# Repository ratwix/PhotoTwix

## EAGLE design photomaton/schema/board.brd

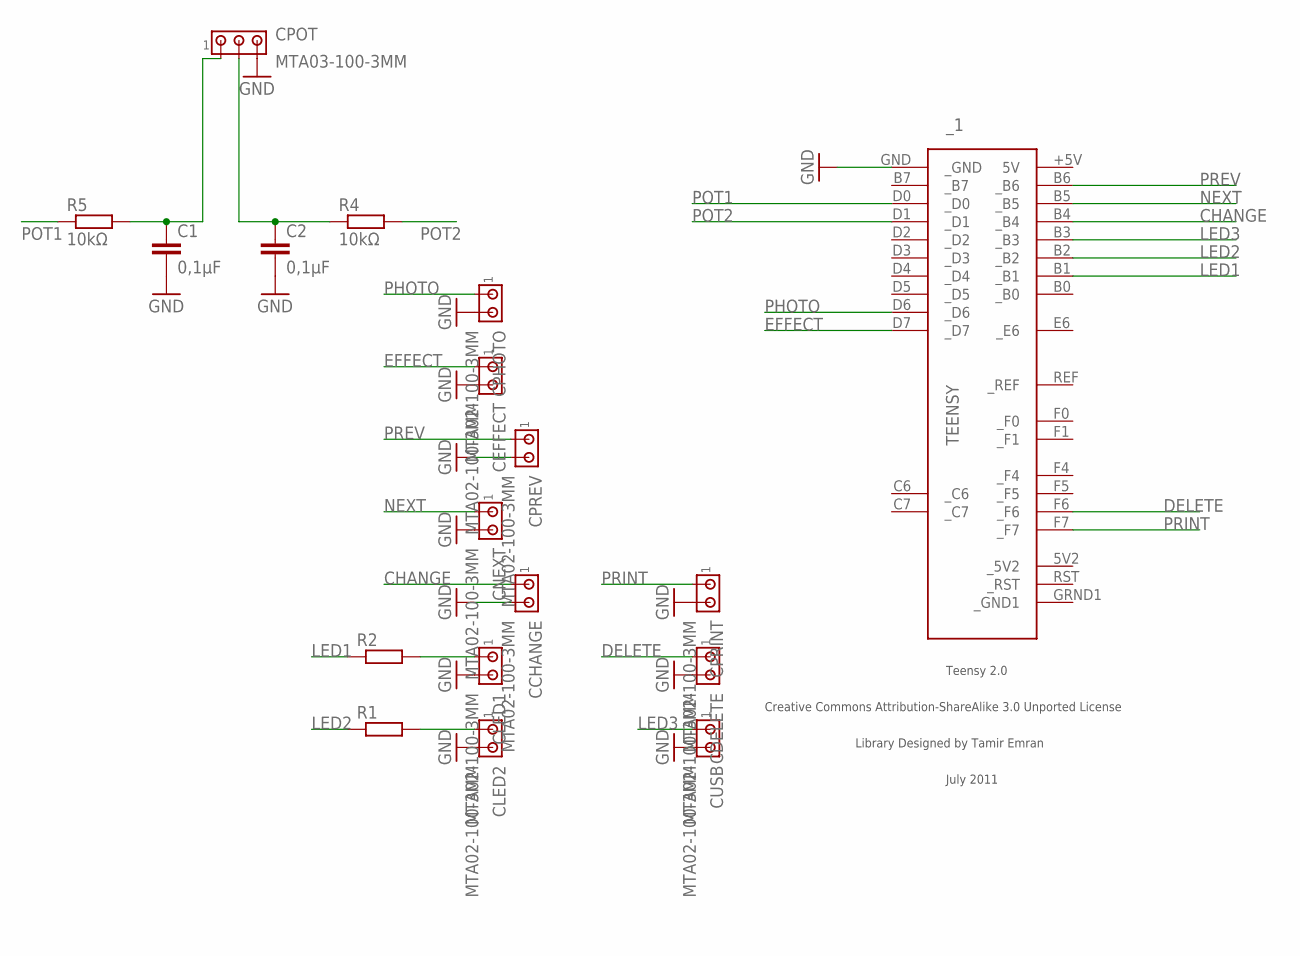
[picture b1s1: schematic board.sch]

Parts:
C1, C2: 0,1µF; C050-025X075
CCHANGE: MTA02-100-3MM; 10X02MTA3MM
CDELETE: MTA02-100-3MM; 10X02MTA3MM
CEFFECT: MTA02-100-3MM; 10X02MTA3MM
CLED1, CLED2: MTA02-100-3MM; 10X02MTA3MM
CNEXT: MTA02-100-3MM; 10X02MTA3MM
CPHOTO: MTA02-100-3MM; 10X02MTA3MM
CPOT: MTA03-100-3MM; 10X03MTA3MM
CPREV: MTA02-100-3MM; 10X02MTA3MM
CPRINT: MTA02-100-3MM; 10X02MTA3MM
CUSB: MTA02-100-3MM; 10X02MTA3MM
R1, R2: R-EU_0204/5; 0204/5
R4, R5: 10kΩ; 0207/7
_1: TEENSY

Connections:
CHANGE: CCHANGE.1, _1.B4 (_B4)
DELETE: CDELETE.1, _1.F6 (_F6)
EFFECT: CEFFECT.1, _1.D7 (_D7)
GND: C1.2, C2.2, CCHANGE.2, CDELETE.2, CEFFECT.2, CLED1.2, CLED2.2, CNEXT.2, CPHOTO.2, CPOT.3, CPREV.2, CPRINT.2, CUSB.2, _1.GND (_GND)
LED1: R2.1, _1.B1 (_B1)
LED2: R1.1, _1.B2 (_B2)
LED3: CUSB.1, _1.B3 (_B3)
unnamed: CLED1.1, R2.2
unnamed: CLED2.1, R1.2
unnamed: C1.1, CPOT.1, R5.2
unnamed: C2.1, CPOT.2, R4.1
NEXT: CNEXT.1, _1.B5 (_B5)
PHOTO: CPHOTO.1, _1.D6 (_D6)
POT1: R5.1, _1.D0 (_D0)
POT2: R4.2, _1.D1 (_D1)
PREV: CPREV.1, _1.B6 (_B6)
PRINT: CPRINT.1, _1.F7 (_F7)

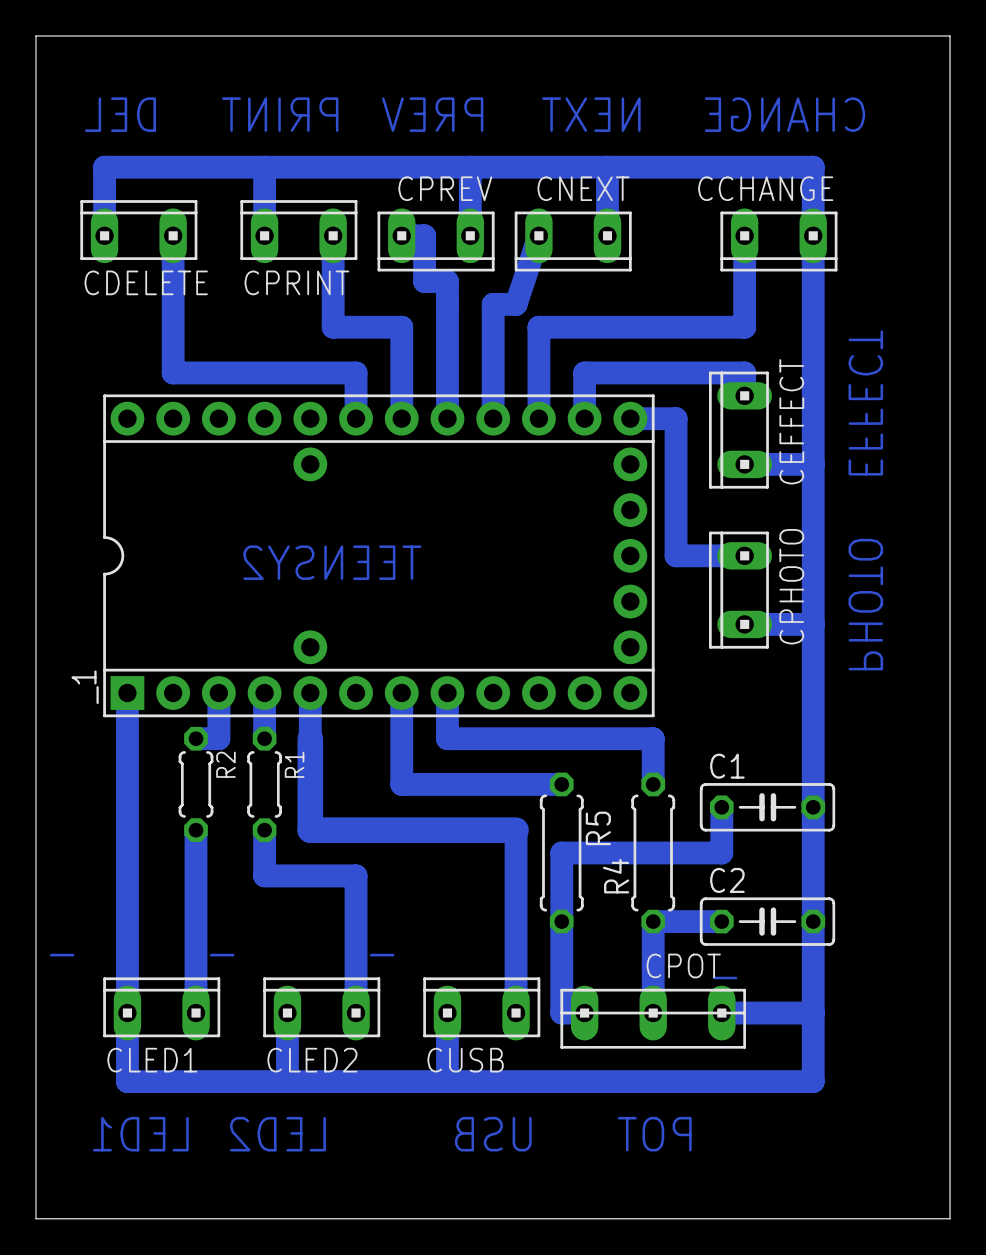
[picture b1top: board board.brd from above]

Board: 2 copper layers, 50.8 x 65.7 mm, 18 parts (0 on the bottom side), 17 nets.

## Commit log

2013-03-07 Photoboot initial import
2013-03-07 Move non web project outside wepapp
2013-03-08 Quelques ajustement
2013-03-12 startup
2013-03-15 Ajout de la copie USB
2013-03-17 style Photomaton
2013-03-17 Bug Polaroid
2013-06-18 1080P
2013-06-18 copyusb
2013-06-19 Change background Add piechart countdown between two photos
2013-06-19 modif de je sais plus quoi
2013-06-20 reduce nb effect improve camera resolution
2013-06-20 Fix timer bug
2013-06-21 correct countdown
2013-06-24 start fix
2013-06-25 Add reset function & refresh button
2013-06-27 Several bugs
2013-06-27 Add poster generation
2013-07-02 Correct many thinks --> no more javascript error Add manual Create poster at the end Correct copy USB Add photo customization
2013-07-04 Update bugs
2013-07-08 Change the galery & workflow process
2013-07-08 Update todo
2013-07-11 Loading page. Bugs USB Colors
2013-07-12 STYLE
2013-07-17 Add administration error
2013-07-17 TODO.txt
2013-09-01 Maj pour V3
2013-09-03 update photo 3

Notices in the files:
parts and their libraries:
teensy: Licensed Under Creative Commons
teensy: Creative Commons Attribution-ShareAlike 3.0 Unported License
teensy: Licensed Under Creative Commons Attribution-ShareAlike 3.0 Unported (CC BY-SA 3.0)
